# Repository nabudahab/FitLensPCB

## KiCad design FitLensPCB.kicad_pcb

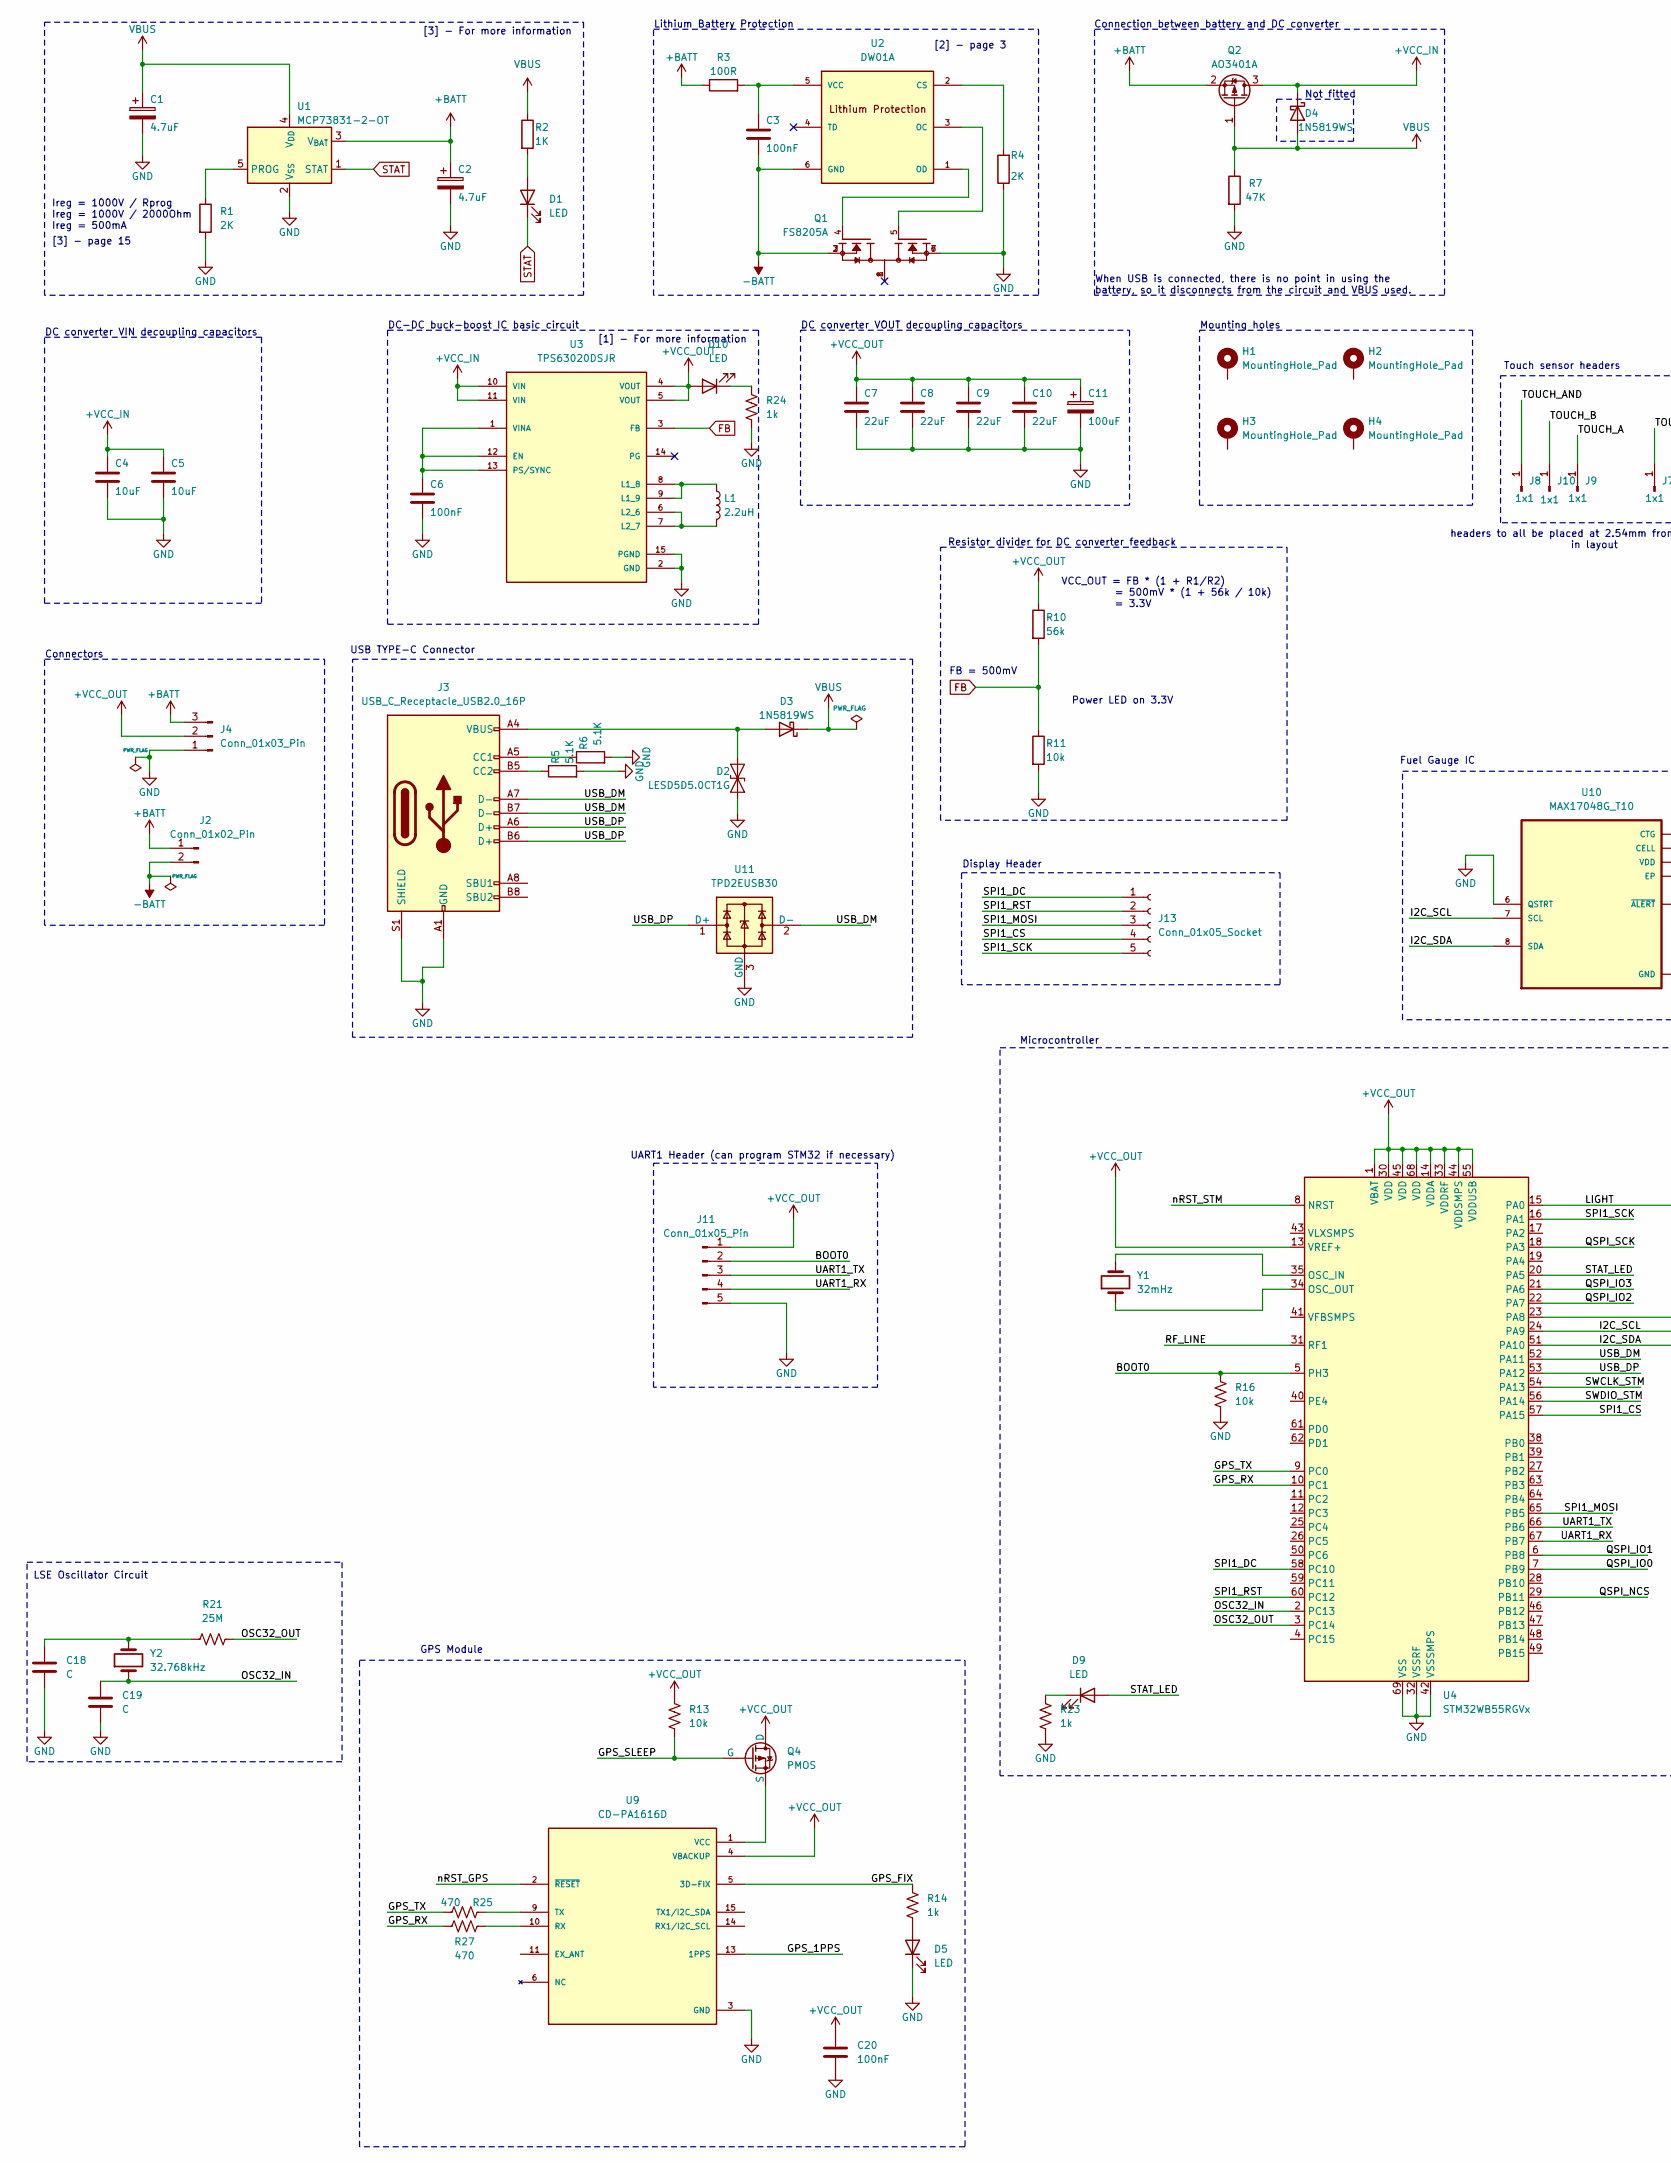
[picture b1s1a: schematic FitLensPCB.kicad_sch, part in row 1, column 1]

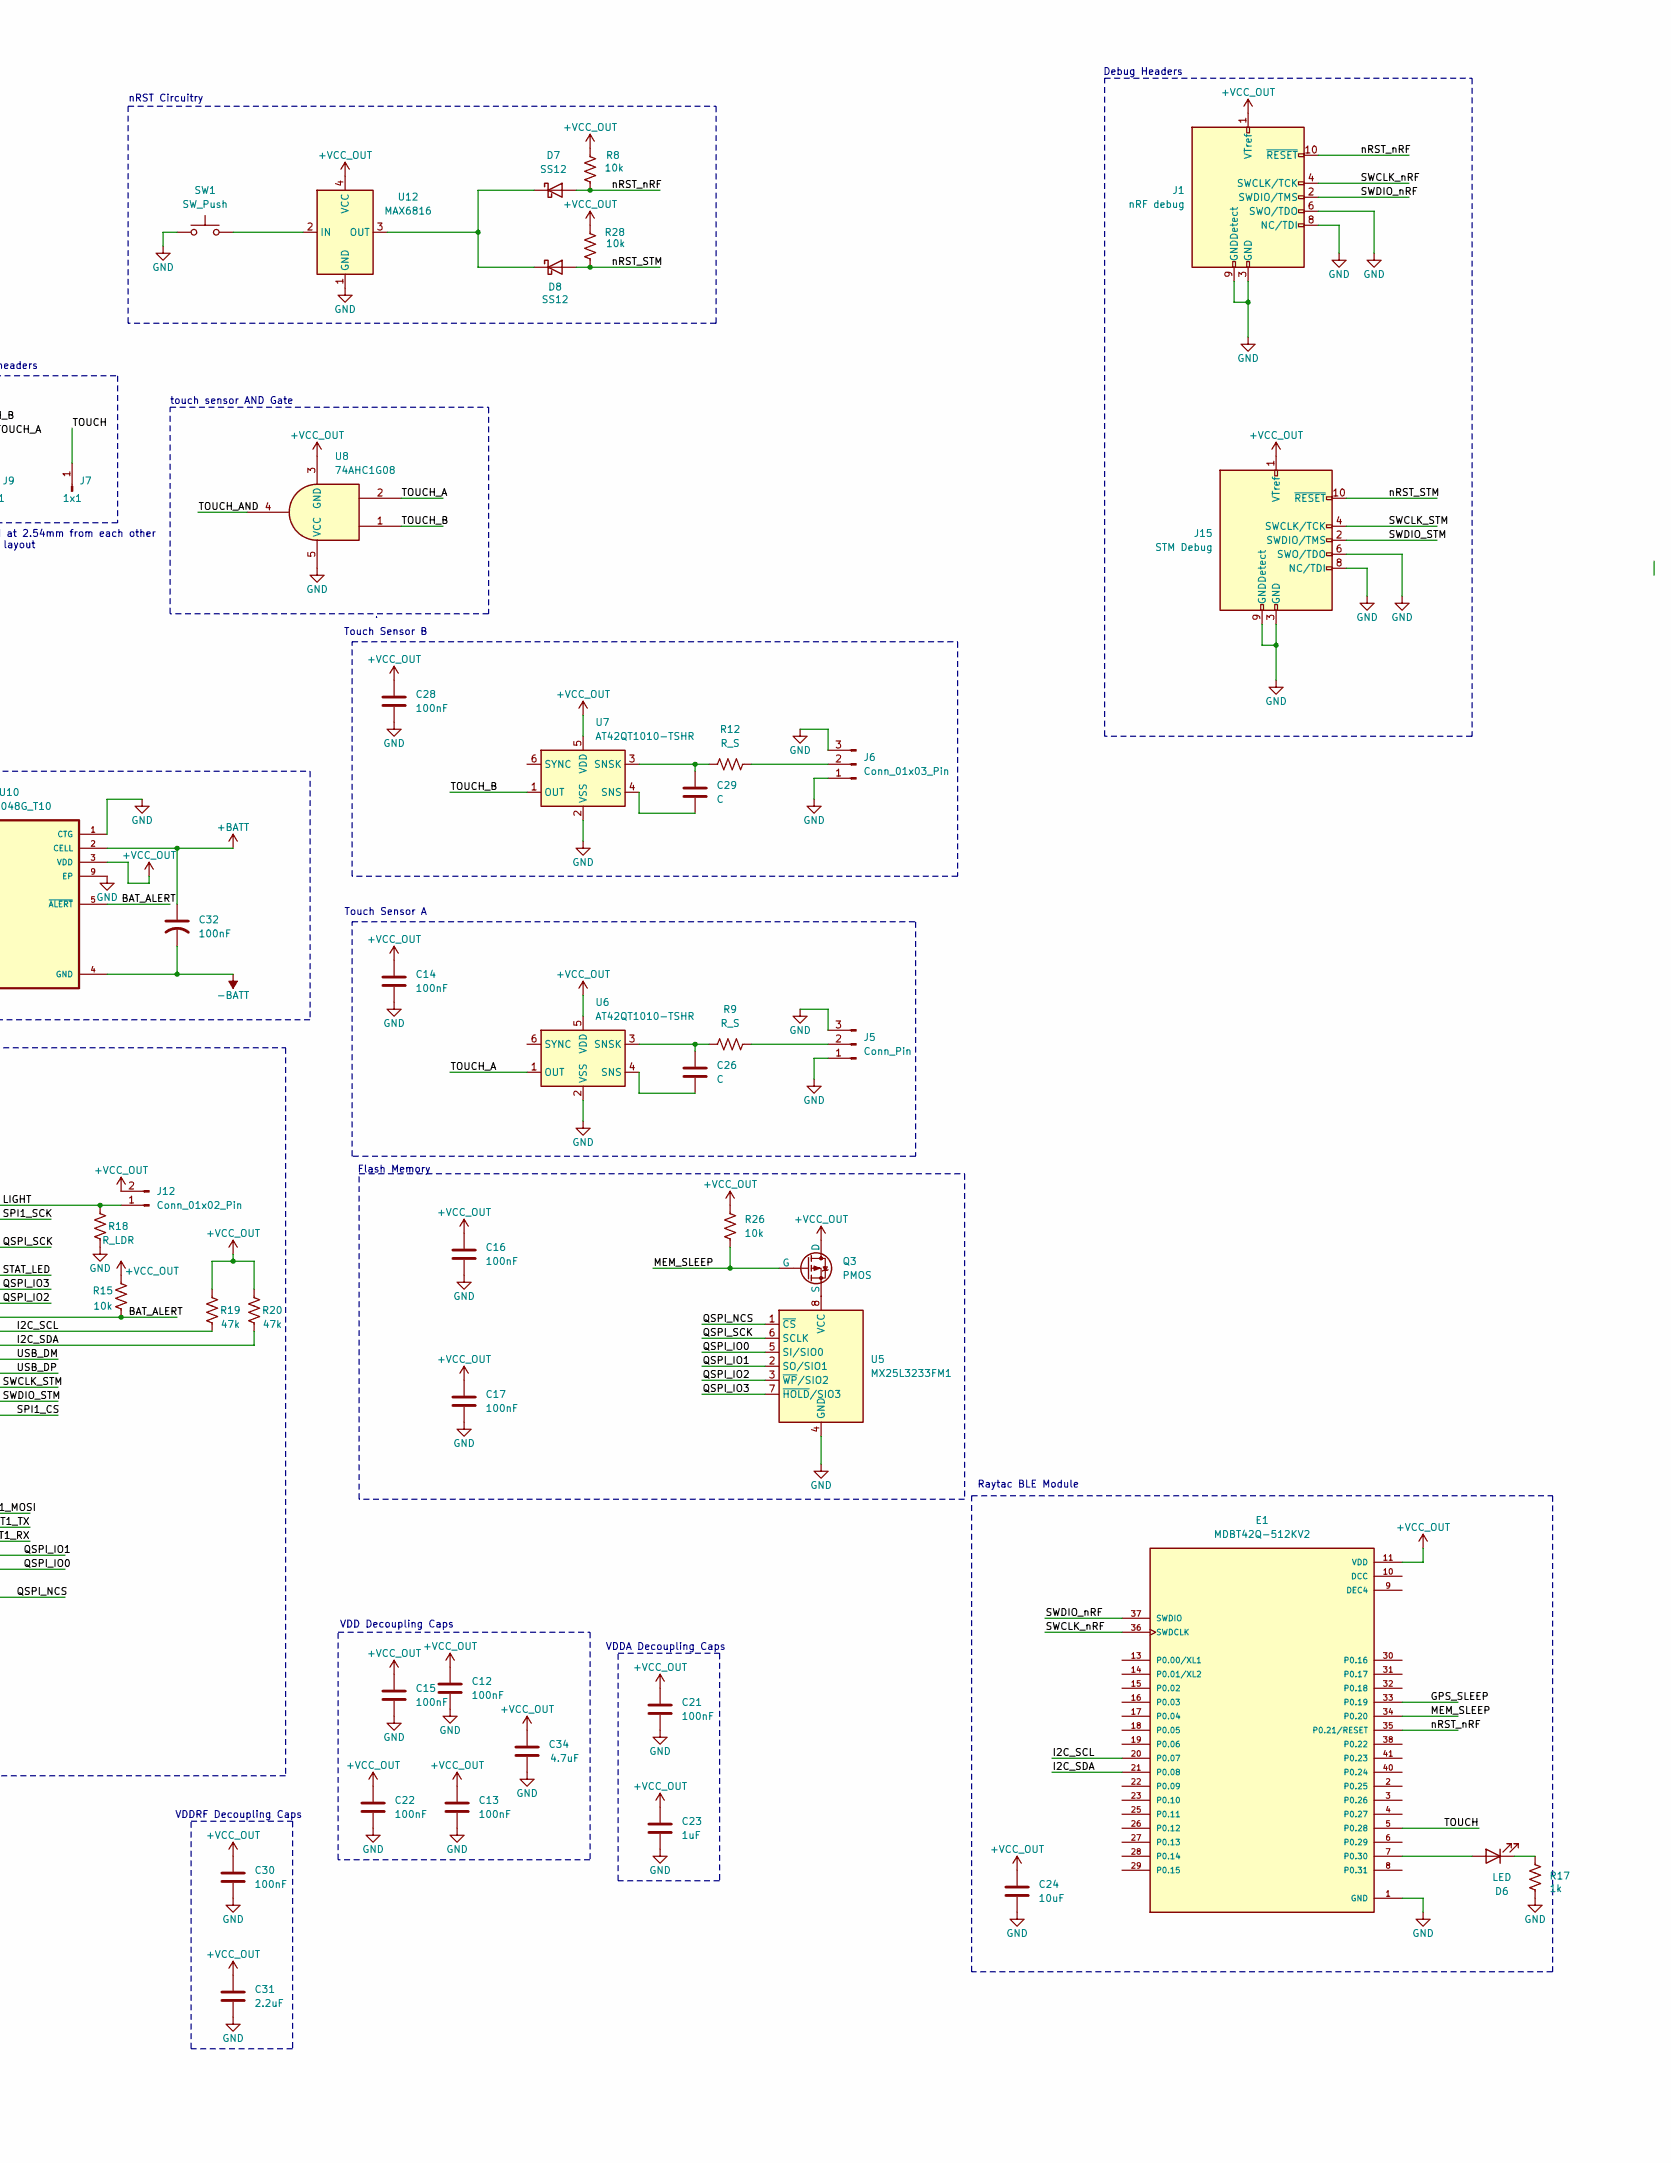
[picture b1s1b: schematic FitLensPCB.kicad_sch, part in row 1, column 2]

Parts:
C1, C2: 4.7uF; CP_EIA-3216-18_Kemet-A
C3, C6, C12, C13, C14, C15, C16, C17, C20, C21, C22, C28, C30, C32: 100nF; C_0805_2012Metric_Pad1.18x1.45mm_HandSolder
C4, C5, C24: 10uF; C_0805_2012Metric_Pad1.18x1.45mm_HandSolder
C7, C8, C9, C10: 22uF; C_0805_2012Metric_Pad1.18x1.45mm_HandSolder
C11: 100uF; CP_EIA-3528-21_Kemet-B
C18, C19, C26, C29: C; C_0805_2012Metric_Pad1.18x1.45mm_HandSolder
C23: 1uF; C_0805_2012Metric_Pad1.18x1.45mm_HandSolder
C31: 2.2uF; C_0805_2012Metric_Pad1.18x1.45mm_HandSolder
C34: 4.7uF; C_0805_2012Metric_Pad1.18x1.45mm_HandSolder
D1: LED; D_SOD-323F
D2: LESD5D5.0CT1G; D_SOD-323F
D3, D4: 1N5819WS; D_SOD-323F
D5: LED; LED_0805_2012Metric
D6, D9, D10: LED; LED_0805_2012Metric_Pad1.15x1.40mm_HandSolder
D7, D8: SS12; D_SOD-123F
E1: MDBT42Q-512KV2; RAYTAC_MDBT42Q-512KV2; PARTREV J
H1, H2, H3, H4: MountingHole_Pad; MountingHole_2.2mm_M2_DIN965_Pad
J1: nRF debug; PinHeader_2x05_P1.27mm_Horizontal
J2: Conn_01x02_Pin; JST_PH_B2B-PH-K_1x02_P2.00mm_Vertical
J3: USB_C_Receptacle_USB2.0_16P; USB_C_Receptacle_GCT_USB4085
J4: Conn_01x03_Pin; JST_EH_B3B-EH-A_1x03_P2.50mm_Vertical
J5: Conn_Pin; JST_XH_S3B-XH-A-1_1x03_P2.50mm_Horizontal
J6: Conn_01x03_Pin; JST_XH_S3B-XH-A-1_1x03_P2.50mm_Horizontal
J7, J8, J9, J10: 1x1; PinHeader_1x01_P2.54mm_Vertical
J11: Conn_01x05_Pin; Hirose_DF13-05P-1.25DS_1x05_P1.25mm_Horizontal
J12: Conn_01x02_Pin; JST_PH_S2B-PH-K_1x02_P2.00mm_Horizontal
J13: Conn_01x05_Socket; Hirose_DF52-5S-0.8H_1x05-1MP_P0.80mm_Horizontal
J15: STM Debug; PinHeader_2x05_P1.27mm_Horizontal
L1: 2.2uH; L_Chilisin_BMRx00060630
Q1: FS8205A; SOP65P640X120-8N; PARTREV 1.7
Q2: AO3401A; SOT-23
Q3, Q4: PMOS; SOT-723
R1, R4: 2K; R_0805_2012Metric_Pad1.20x1.40mm_HandSolder
R2: 1K; R_0805_2012Metric_Pad1.20x1.40mm_HandSolder
R3: 100R; R_0805_2012Metric_Pad1.20x1.40mm_HandSolder
R5, R6: 5.1K; R_0805_2012Metric_Pad1.20x1.40mm_HandSolder
R7: 47K; R_0805_2012Metric_Pad1.20x1.40mm_HandSolder
R8, R11, R13, R15, R16, R26, R28: 10k; R_0805_2012Metric_Pad1.20x1.40mm_HandSolder
R9, R12: R_S; R_0805_2012Metric_Pad1.20x1.40mm_HandSolder
R10: 56k; R_0805_2012Metric_Pad1.20x1.40mm_HandSolder
R14, R24: 1k; R_0805_2012Metric_Pad1.20x1.40mm_HandSolder
R17, R23: 1k; R_0805_2012Metric
R18: R_LDR; R_0805_2012Metric_Pad1.20x1.40mm_HandSolder
R19, R20: 47k; R_0805_2012Metric_Pad1.20x1.40mm_HandSolder
R21: 25M; R_0805_2012Metric_Pad1.20x1.40mm_HandSolder
R25, R27: 470; R_0805_2012Metric_Pad1.20x1.40mm_HandSolder
SW1: SW_Push; SW_SPST_CK_RS282G05A3
U1: MCP73831-2-OT; SOT95P280X145-5N
U2: DW01A; SOT95P280X145-6N; M_PART_NUMBER DW01A
U3: TPS63020DSJR; IC_TPS63020DSJR
U4: STM32WB55RGVx; QFN-68-1EP_8x8mm_P0.4mm_EP6.4x6.4mm
U5: MX25L3233FM1; SOIC127P790X216-8N_MX25L3233FM2I-08G
U6, U7: AT42QT1010-TSHR; SOT-23-6
U8: 74AHC1G08; SOT-23-5_HandSoldering
U9: CD-PA1616D; XCVR_CD-PA1616D; PARTREV V.06
U10: MAX17048G_T10; SON50P200X200X80-9N; DigiKey_Part_Number MAX17048G+T10CT-ND
U11: TPD2EUSB30; Texas_DRT-3
U12: MAX6816; SOT-143
Y1: 32mHz; Crystal_SMD_0603-2Pin_6.0x3.5mm_HandSoldering
Y2: 32.768kHz; Crystal_SMD_FOX_FE-2Pin_7.5x5.0mm_HandSoldering

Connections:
+BATT: C2.1, C32.1, J2.1, J4.3, Q2.2 (S), R3.1, U1.3 (V_{BAT}), U10.2 (CELL)
+VCC_IN: C4.1, C5.1, D4.1 (K), Q2.3 (D), U3.10 (VIN), U3.11 (VIN)
+VCC_OUT: C7.1, C8.1, C9.1, C10.1, C11.1, C12.1, C13.1, C14.1, C15.1, C16.1, C17.1, C20.1, C21.1, C22.1, C23.1, C24.1, C28.1, C30.1, C31.1, C34.1, D10.2 (A), E1.11 (VDD), J1.1 (VTref), J4.2, J11.1, J12.2, J15.1 (VTref), Q3.1 (D), Q4.1 (D), R8.1, R10.1, R13.1, R15.2, R19.2, R20.2, R26.1, R28.1, U3.4 (VOUT), U3.5 (VOUT), U4.1 (VBAT), U4.13 (VREF+), U4.14 (VDDA), U4.30 (VDD), U4.33 (VDDRF), U4.44 (VDDSMPS), U4.45 (VDD), U4.55 (VDDUSB), U4.68 (VDD), U6.5 (VDD), U7.5 (VDD), U8.3 (GND), U9.4 (VBACKUP), U10.3 (VDD), U12.4 (VCC)
-BATT: C3.2, C32.2, J2.2, Q1.2, Q1.3, U2.6 (GND), U10.4 (GND)
/BAT_ALERT: R15.1, U4.23 (PA8), U10.5 (~ALERT)
/BOOT0: J11.2, R16.1, U4.5 (PH3)
/GPS_1PPS: U9.13 (1PPS)
/GPS_FIX: R14.1, U9.5 (3D-FIX)
/GPS_RX: R27.1, U4.10 (PC1)
/GPS_SLEEP: E1.33 (P0.19), Q4.2 (G), R13.2
/GPS_TX: R25.1, U4.9 (PC0)
/I2C_SCL: E1.20 (P0.07), R19.1, U4.24 (PA9), U10.7 (SCL)
/I2C_SDA: E1.21 (P0.08), R20.1, U4.51 (PA10), U10.8 (SDA)
/LIGHT: J12.1, R18.2, U4.15 (PA0)
/MEM_SLEEP: E1.34 (P0.20), Q3.2 (G), R26.2
/OSC32_IN: C19.1, U4.2 (PC13), Y2.1
/OSC32_OUT: R21.2, U4.3 (PC14)
/QSPI_IO0: U4.7 (PB9), U5.5 (SI/SIO0)
/QSPI_IO1: U4.6 (PB8), U5.2 (SO/SIO1)
/QSPI_IO2: U4.22 (PA7), U5.3 (~WP/SIO2)
/QSPI_IO3: U4.21 (PA6), U5.7 (~HOLD/SIO3)
/QSPI_NCS: U4.29 (PB11), U5.1 (~CS)
/QSPI_SCK: U4.18 (PA3), U5.6 (SCLK)
/RF_LINE: U4.31 (RF1)
/SPI1_CS: J13.4, U4.57 (PA15)
/SPI1_DC: J13.1, U4.58 (PC10)
/SPI1_MOSI: J13.3, U4.65 (PB5)
/SPI1_RST: J13.2, U4.60 (PC12)
/SPI1_SCK: J13.5, U4.16 (PA1)
/STAT_LED: D9.2 (A), U4.20 (PA5)
/SWCLK_STM: J15.4 (SWCLK/TCK), U4.54 (PA13)
/SWCLK_nRF: E1.36 (SWDCLK), J1.4 (SWCLK/TCK)
/SWDIO_STM: J15.2 (SWDIO/TMS), U4.56 (PA14)
/SWDIO_nRF: E1.37 (SWDIO), J1.2 (SWDIO/TMS)
/TOUCH: E1.5 (P0.28), J7.1
/TOUCH_A: J9.1, U6.1 (OUT), U8.2
/TOUCH_AND: J8.1, U8.4
/TOUCH_B: J10.1, U7.1 (OUT), U8.1
/UART1_RX: J11.4, U4.67 (PB7)
/UART1_TX: J11.3, U4.66 (PB6)
/USB_DM: J3.A7 (D-), J3.B7 (D-), U4.52 (PA11), U11.2 (D-)
/USB_DP: J3.A6 (D+), J3.B6 (D+), U4.53 (PA12), U11.1 (D+)
/nRST_GPS: U9.2 (~RESET)
/nRST_STM: D8.2 (A), J15.10 (~RESET), R28.2, U4.8 (NRST)
/nRST_nRF: D7.2 (A), E1.35 (P0.21/RESET), J1.10 (~RESET), R8.2
FB: R10.2, R11.1, U3.3 (FB)
GND: C1.2, C2.2, C4.2, C5.2, C6.2, C7.2, C8.2, C9.2, C10.2, C11.2, C12.2, C13.2, C14.2, C15.2, C16.2, C17.2, C18.2, C19.2, C20.2, C21.2, C22.2, C23.2, C24.2, C28.2, C30.2, C31.2, C34.2, D2.1 (A1), D5.1 (K), E1.1 (GND), E1.12 (GND), E1.24 (GND), E1.39 (GND), J1.3 (GND), J1.5 (GND), J1.6 (SWO/TDO), J1.8 (NC/TDI), J1.9 (GNDDetect), J3.A1 (GND), J3.A12 (GND), J3.B1 (GND), J3.B12 (GND), J3.S1 (SHIELD), J4.1, J5.1, J5.3, J6.1, J6.3, J11.5, J15.3 (GND), J15.5 (GND), J15.6 (SWO/TDO), J15.8 (NC/TDI), J15.9 (GNDDetect), Q1.6, Q1.7, R1.2, R4.1, R5.2, R6.2, R7.2, R11.2, R16.2, R17.1, R18.1, R23.1, R24.2, SW1.1, U1.2 (V_{SS}), U3.2 (GND), U3.15 (PGND), U4.32 (VSSRF), U4.42 (VSSSMPS), U4.69 (VSS), U5.4 (GND), U6.2 (VSS), U7.2 (VSS), U8.5 (VCC), U9.3 (GND), U9.8 (GND), U9.12 (GND), U9.19 (GND), U10.1 (CTG), U10.6 (QSTRT), U10.9 (EP), U11.3 (GND), U12.1 (GND)
unnamed: C18.1, R21.1, Y2.2
unnamed: D1.2 (A), R2.2
unnamed: D2.2 (A2), D3.2 (A), J3.A4 (VBUS), J3.A9 (VBUS), J3.B4 (VBUS), J3.B9 (VBUS)
unnamed: D5.2 (A), R14.2
unnamed: D6.2 (A), E1.7 (P0.30)
unnamed: D6.1 (K), R17.2
unnamed: D7.1 (K), D8.1 (K), U12.3 (OUT)
unnamed: D9.1 (K), R23.2
unnamed: D10.1 (K), R24.1
unnamed: J3.A5 (CC1), R6.1
unnamed: J3.B5 (CC2), R5.1
unnamed: J5.2, R9.2
unnamed: J6.2, R12.2
unnamed: Q3.3 (S), U5.8 (VCC)
unnamed: Q4.3 (S), U9.1 (VCC)
unnamed: R1.1, U1.5 (PROG)
unnamed: R4.2, U2.2 (CS)
unnamed: Q1.5, U2.3 (OC)
unnamed: Q1.4, U2.1 (OD)
unnamed: C3.1, R3.2, U2.5 (VCC)
unnamed: C6.1, U3.1 (VINA), U3.12 (EN), U3.13 (PS/SYNC)
unnamed: L1.1, U3.8 (L1_8), U3.9 (L1_9)
unnamed: L1.2, U3.6 (L2_6), U3.7 (L2_7)
unnamed: U4.35 (OSC_IN), Y1.2
unnamed: U4.34 (OSC_OUT), Y1.1
unnamed: C26.2, U6.4 (SNS)
unnamed: C26.1, R9.1, U6.3 (SNSK)
unnamed: C29.2, U7.4 (SNS)
unnamed: C29.1, R12.1, U7.3 (SNSK)
unnamed: R27.2, U9.10 (RX)
unnamed: R25.2, U9.9 (TX)
unnamed: SW1.2, U12.2 (IN)
STAT: D1.1 (K), U1.1 (STAT)
VBUS: C1.1, D3.1 (K), D4.2 (A), Q2.1 (G), R2.1, R7.1, U1.4 (V_{DD})

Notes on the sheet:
Connection between battery and DC converter
LSE Oscillator Circuit
Debug Headers
Touch Sensor B
[1] - For more information
[3] - page 15
touch sensor AND Gate
FB = 500mV
VDD Decoupling Caps
When USB is connected, there is no point in using the battery, so it disconnects from the circuit and VBUS used.
DC-DC buck-boost IC basic circuit
nRST Circuitry
Not fitted
Ireg = 1000V / Rprog Ireg = 1000V / 2000Ohm Ireg = 500mA
Raytac BLE Module
[3] - For more information
Touch sensor headers
USB TYPE-C Connector
Fuel Gauge IC
Connectors
DC converter VIN decoupling capacitors
Power LED on 3.3V
headers to all be placed at 2.54mm from each other in layout
Resistor divider for DC converter feedback
GPS Module
VDDRF Decoupling Caps
Display Header
Touch Sensor A
DC converter VOUT decoupling capacitors
Microcontroller
Mounting holes
Lithium Battery Protection
VDDA Decoupling Caps
Flash Memory
VCC_OUT = FB * (1 + R1/R2) = 500mV * (1 + 56k / 10k) = 3.3V
UART1 Header (can program STM32 if necessary)
[2] - page 3

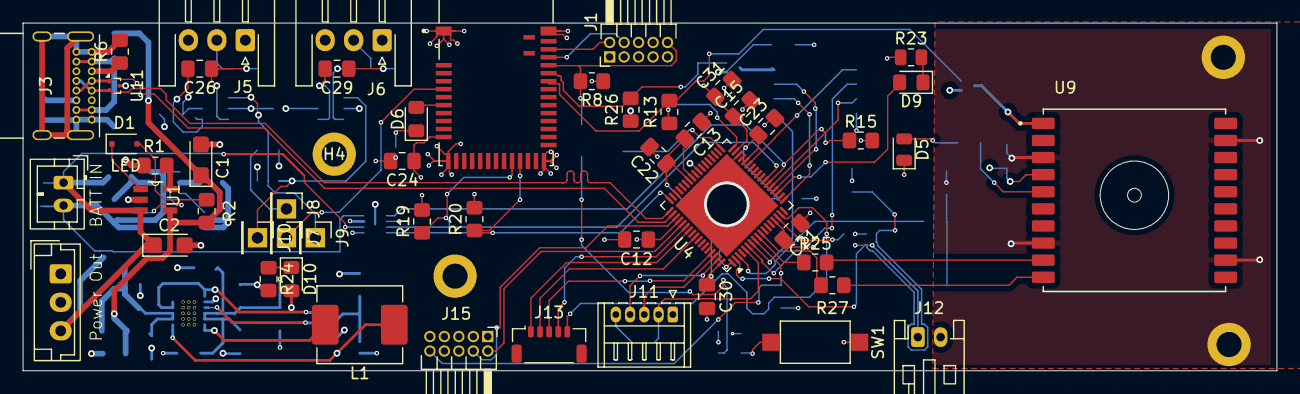
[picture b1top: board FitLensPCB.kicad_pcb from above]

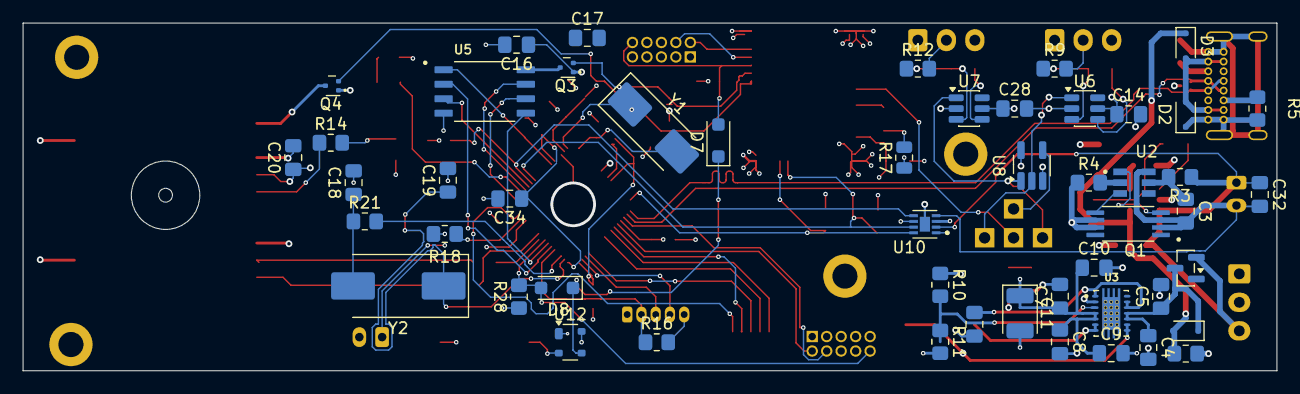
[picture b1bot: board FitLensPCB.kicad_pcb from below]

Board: 4 copper layers, 110.0 x 30.5 mm, 107 parts (51 on the bottom side), 78 nets.

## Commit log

2026-01-28 complete most of schematic
2026-02-16 I dont even know anymore
2026-02-16 complete schematic allegedly
2026-02-17 screw this
2026-02-23 complete PCB
2026-03-03 implement some feedback
